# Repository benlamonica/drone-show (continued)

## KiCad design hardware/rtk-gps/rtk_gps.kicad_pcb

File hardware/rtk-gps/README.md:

# RTK GPS board, rev A

NEO-F10N-00B-20 (L1/L5 raw carrier phase) feeds an RP2350A running RTKLIB, which outputs the fix to the flight controller. An MMC5983MA compass sits on the FC's I2C bus.

- 2-layer board, 45 x 45 x 1.6 mm, corner radius 1.5 mm. 4x M2 holes (2.2 mm) on a 39 mm square, 3 mm in from each edge. All parts are on the top side and the smallest passive is 0603.
- PCBWay rules are in `rtk_gps.kicad_dru` and the project file: 0.15 mm (6 mil) track and space, 0.3/0.65 mm vias, 0.3 mm copper to edge.
- DRC: 0 errors and 0 unconnected; schematic parity is clean. One connection_width warning (a 0.13 mm neck at U1 pin 44, +3V3) and silk-clipped-by-mask warnings remain.
- ERC: clean.

## Connectors
| Ref | Part | Pins |
|---|---|---|
| J1 | JST GH-6, Pixhawk GPS port | 1 +5V, 2 FC_TX (into RP2350 GP5), 3 FC_RX (from GP4), 4 SCL, 5 SDA, 6 GND |
| J2 | JST GH-4, AUX UART (RTCM in) | 1 +5V, 2 AUX_TX (GP8), 3 AUX_RX (GP9), 4 GND |
| J3 | JST SH-3, SWD | Raspberry Pi Debug Probe pinout |
| J4 | U.FL | active antenna, 3.3 V bias through 10R + 27nH |
| J5 | USB-C | flashing/debug; diode-ORed with J1 5V |

## RP2350 pins
GP0 TX to GNSS RXD, GP1 RX from GNSS TXD, GP2 PPS, GP3 GNSS reset, GP4/GP5 UART1 to FC, GP6 EXTINT, GP8/GP9 AUX UART (PIO), GP25 status LED. SW1 is BOOTSEL and SW2 is RESET.

## Notes
- Compass: ArduPilot detects the MMC5983MA (I2C 0x30) as an external compass on the GPS I2C bus. The footprint is based on KiCad's MMC5883MA LGA-16 3x3 footprint, which has the same pin map. Check it against the MMC5983MA datasheet land pattern before ordering.
- Antenna: Taoglas AGVLB.25B.07.0060A (L1/L5 helical, U.FL, Mouser 960-AGVLB.25B070060A) is the suggested replacement for an L1-only helical.
- The firmware needs a GPS+Galileo+BeiDou, L1/L5 build (NFREQ=2); the NEO-F10N has no GLONASS.
- The J2 connector (SM04B-GHS-TB) is on backorder at Mouser until about Feb 2027. Any JST GH 4-pin horizontal SMT part fits, or leave J2 off if corrections come through the FC on J1.

## Regenerating
The scripts in `gen/` build everything from `gen/design.py`. They run in the kicad/kicad:9.0 docker image with Freerouting 1.9: `build.sh` does a full re-route, `post.sh` reuses the existing routes, and `gen/export.sh` writes `fab/`.

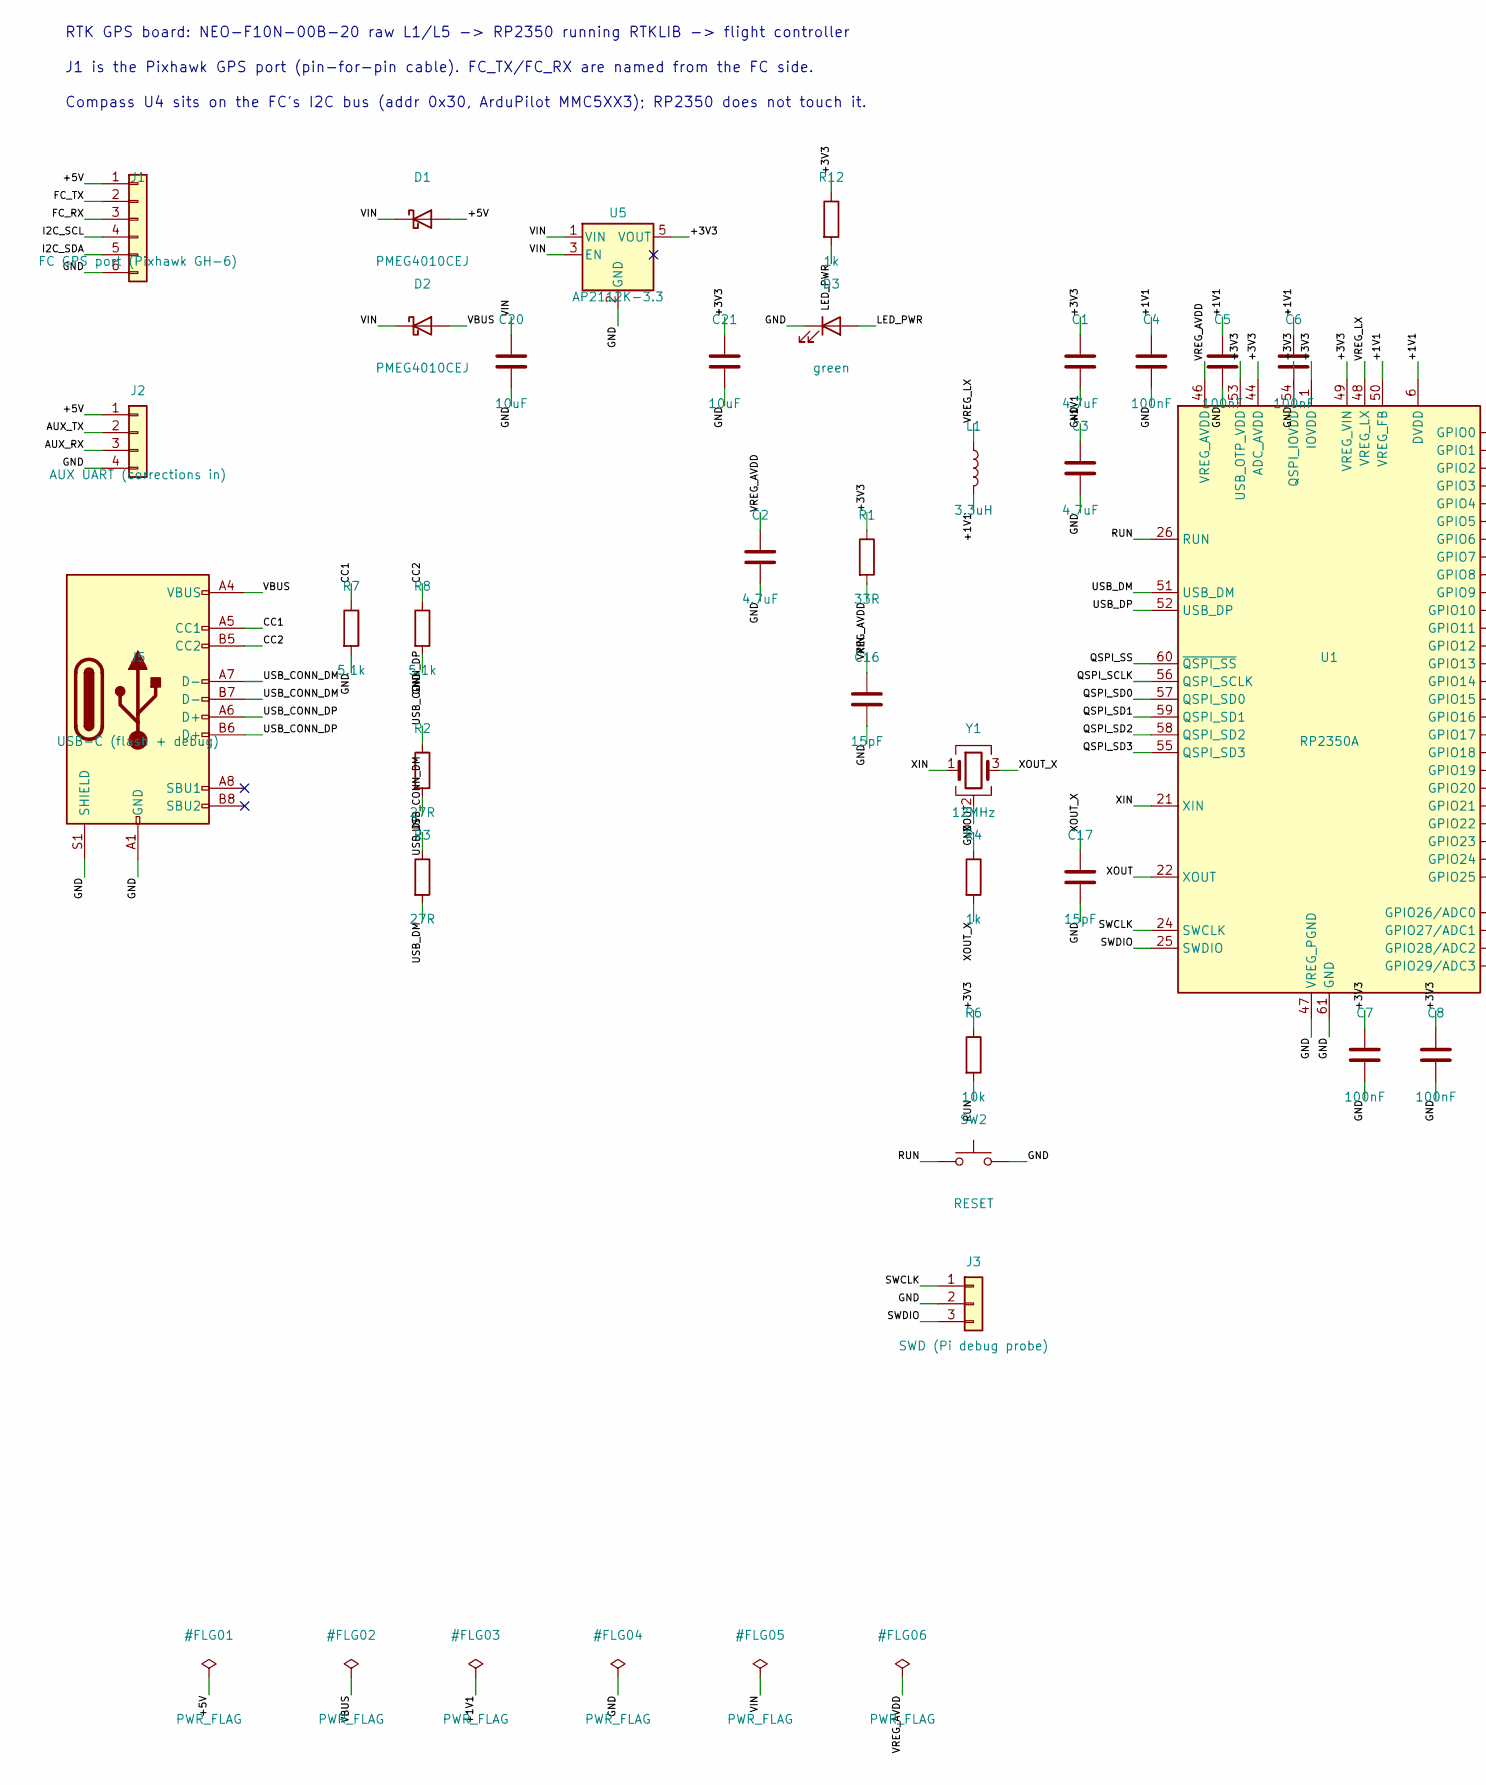
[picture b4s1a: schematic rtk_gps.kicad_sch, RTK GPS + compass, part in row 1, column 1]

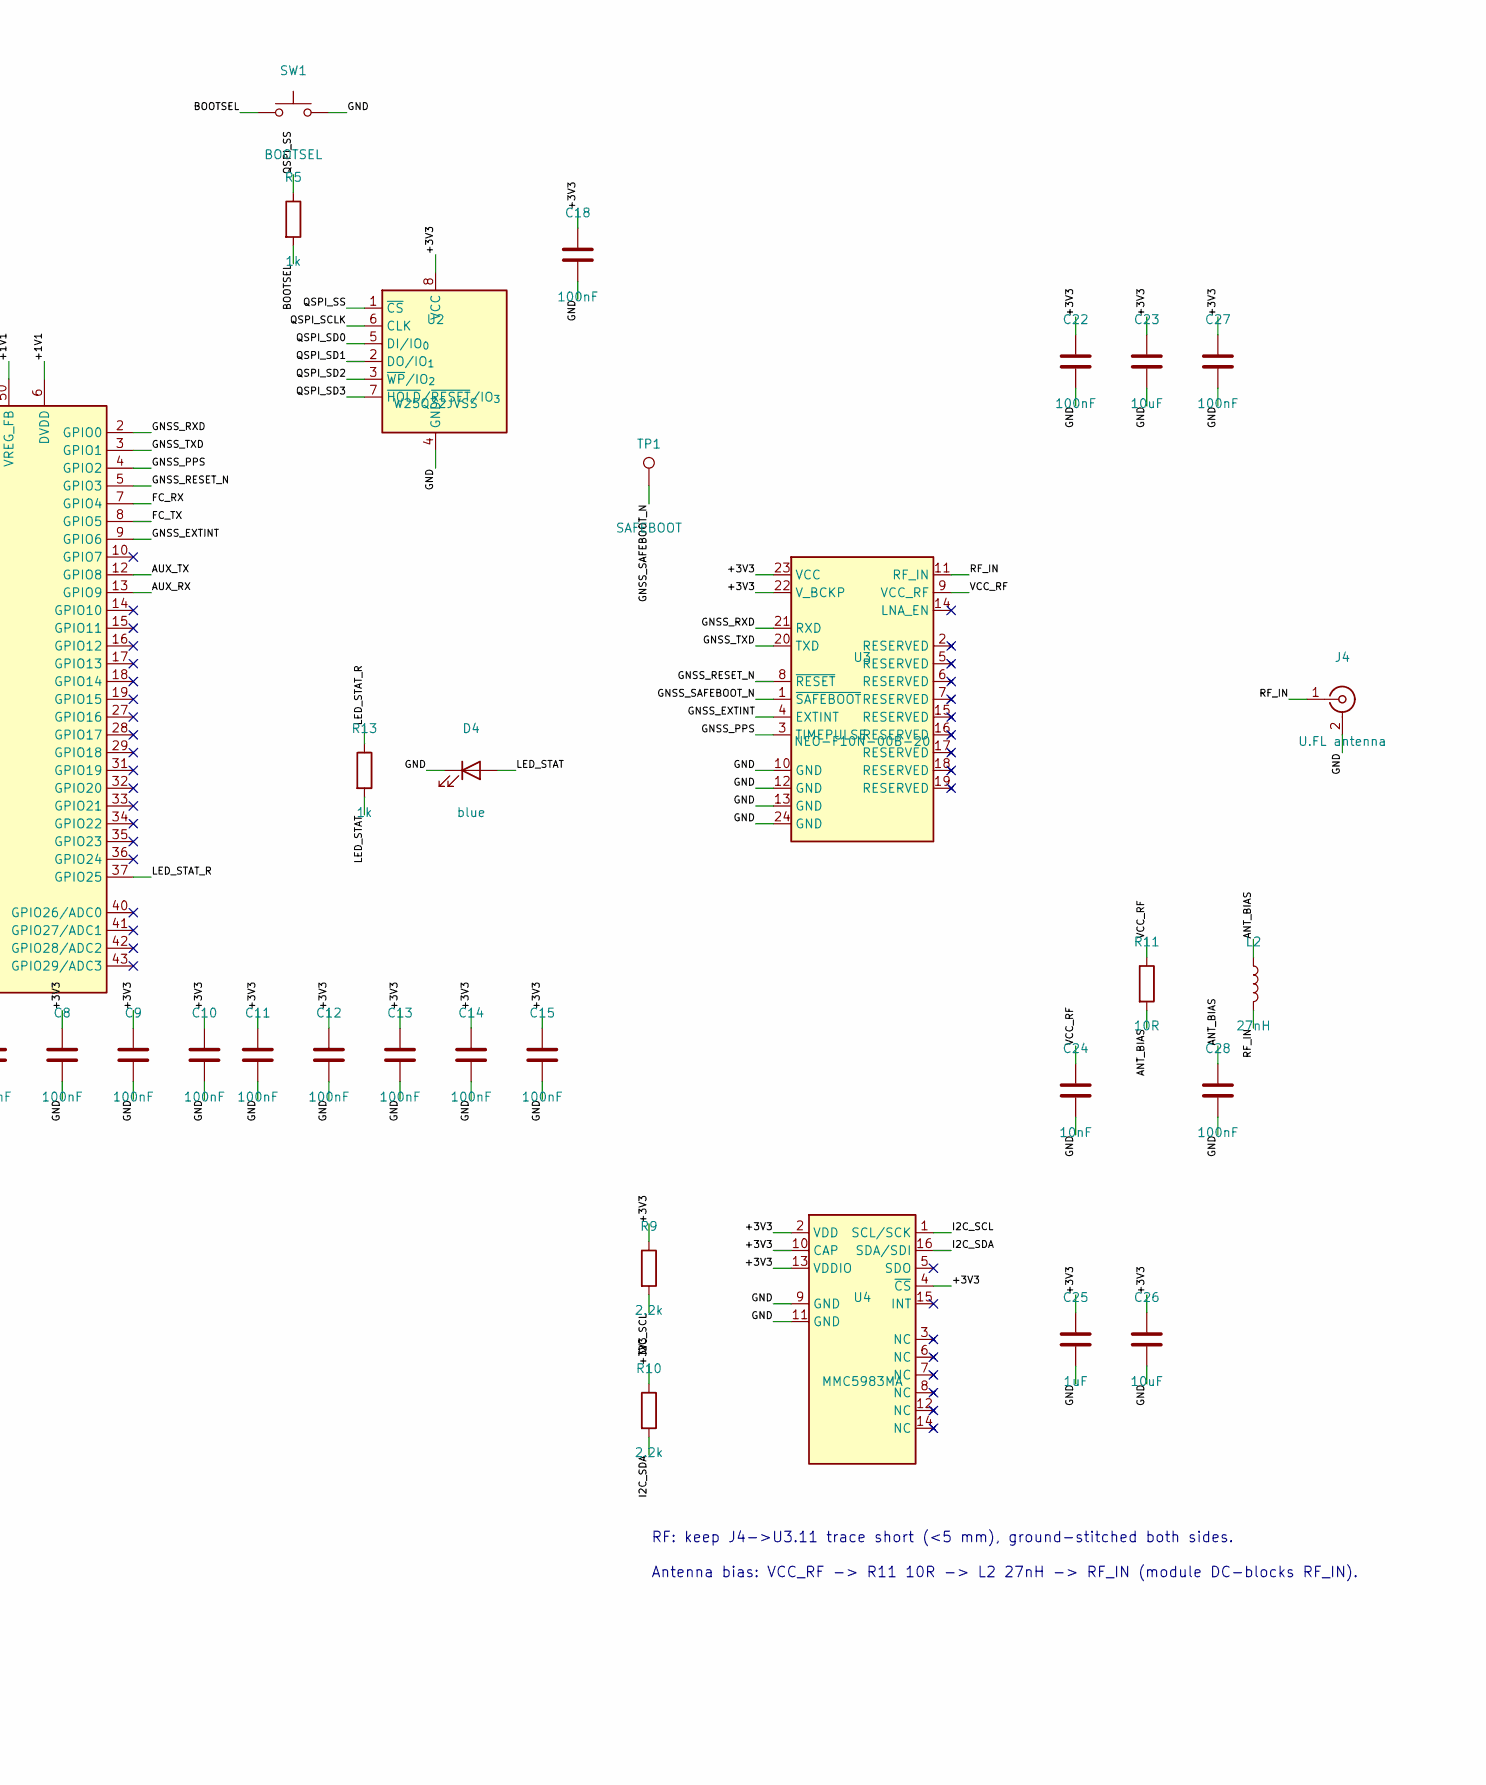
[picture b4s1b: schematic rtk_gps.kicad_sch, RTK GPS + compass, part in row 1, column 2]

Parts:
C1, C2, C3: 4.7uF; C_0603_1608Metric; MPN CL10A475MO8NNNC; Mouser 187-CL10A475MO8NNNC
C4, C5, C6, C7, C8, C9, C10, C11, C12, C13, C14, C15, C18, C22, C27, C28: 100nF; C_0603_1608Metric; MPN CC0603KRX7R7BB104; Mouser 603-CC603KRX7R7BB104
C16, C17: 15pF; C_0603_1608Metric; MPN CC0603JRNPO9BN150; Mouser 603-CC603JRNPO9BN150
C20, C21: 10uF; C_0805_2012Metric; MPN CC0805KKX5R7BB106; Mouser 603-CC805KKX5R7BB106
C23, C26: 10uF; C_0603_1608Metric; MPN LMK107BBJ106MALT; Mouser 963-LMK107BBJ106MALT
C24: 10nF; C_0603_1608Metric; MPN CC0603KRX7R9BB103; Mouser 603-CC603KRX7R9BB103
C25: 1uF; C_0603_1608Metric; MPN CC0603KRX7R7BB105; Mouser 603-CC603KRX7R7BB105
D1, D2: PMEG4010CEJ; D_SOD-323F; MPN PMEG4010CEJ,115; Mouser 771-PMEG4010CEJ-T/R
D3: green; LED_0603_1608Metric; MPN LTST-C191KGKT; Mouser 859-LTST-C191KGKT
D4: blue; LED_0603_1608Metric; MPN LTST-C191TBKT; Mouser 859-LTST-C191TBKT
J1: FC GPS port (Pixhawk GH-6); JST_GH_SM06B-GHS-TB_1x06-1MP_P1.25mm_Horizontal; MPN SM06B-GHS-TB(LF)(SN); Mouser 306-SM06BGHSTBLFSN
J2: AUX UART (corrections in); JST_GH_SM04B-GHS-TB_1x04-1MP_P1.25mm_Horizontal; MPN SM04B-GHS-TB(LF)(SN); Mouser 306-SM04BGHSTBLFSN
J3: SWD (Pi debug probe); JST_SH_SM03B-SRSS-TB_1x03-1MP_P1.00mm_Horizontal; MPN SM03B-SRSS-TB(LF)(SN); Mouser 306-SM03BSRSSTBLFSNP
J4: U.FL antenna; U.FL_Hirose_U.FL-R-SMT-1_Vertical; MPN U.FL-R-SMT-1(10); Mouser 798-U.FL-R-SMT-1-10
J5: USB-C (flash + debug); USB_C_Receptacle_GCT_USB4105-xx-A_16P_TopMnt_Horizontal; MPN USB4105-GF-A; Mouser 640-USB4105-GF-A
L1: 3.3uH; L_Murata_DFE201610P; MPN AOTA-B201610S3R3-101-T; Mouser 815-AB201610S3R3101T
L2: 27nH; L_0603_1608Metric; MPN LQG18HN27NJ00D; Mouser 81-LQG18HN27NJ00D
R1: 33R; R_0603_1608Metric; MPN RC0603FR-0733RL; Mouser 603-RC0603FR-0733RL
R2, R3: 27R; R_0603_1608Metric; MPN RC0603FR-0727RL; Mouser 603-RC0603FR-0727RL
R4, R5, R12, R13: 1k; R_0603_1608Metric; MPN RC0603FR-071KL; Mouser 603-RC0603FR-071KL
R6: 10k; R_0603_1608Metric; MPN RC0603FR-0710KL; Mouser 603-RC0603FR-0710KL
R7, R8: 5.1k; R_0603_1608Metric; MPN RC0603FR-075K1L; Mouser 603-RC0603FR-075K1L
R9, R10: 2.2k; R_0603_1608Metric; MPN RC0603FR-072K2L; Mouser 603-RC0603FR-072K2L
R11: 10R; R_0603_1608Metric; MPN RC0603FR-0710RL; Mouser 603-RC0603FR-0710RL
SW1: BOOTSEL; SW_SPST_B3U-1000P; MPN B3U-1000P; Mouser 653-B3U-1000P
SW2: RESET; SW_SPST_B3U-1000P; MPN B3U-1000P; Mouser 653-B3U-1000P
TP1: SAFEBOOT; TestPoint_Pad_D1.0mm
U1: RP2350A; QFN-60-1EP_7x7mm_P0.4mm_EP3.4x3.4mm; MPN SC1509-A4 (RP2350A); Mouser 358-SC1509
U2: W25Q32JVSS; SOIC-8_5.3x5.3mm_P1.27mm; MPN W25Q32JVSSIQ; Mouser 454-W25Q32JVSSIQ
U3: NEO-F10N-00B-20; ublox_NEO; MPN NEO-F10N-00B-20; Mouser 377-NEO-F10N-00B-20
U4: MMC5983MA; LGA-16_3x3mm_P0.5mm; MPN MMC5983MA; Mouser 438-MMC5983MA
U5: AP2112K-3.3; SOT-23-5; MPN AP2112K-3.3TRG1; Mouser 621-AP2112K-3.3TRG1
Y1: 12MHz; Crystal_SMD_3225-4Pin_3.2x2.5mm; MPN ABM8-272-T3; Mouser 815-ABM8-272-T3

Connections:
/+1V1: C3.1, C4.1, C5.1, C6.1, L1.2, U1.6 (DVDD), U1.23 (DVDD), U1.39 (DVDD), U1.50 (VREG_FB)
/+3V3: C1.1, C7.1, C8.1, C9.1, C10.1, C11.1, C12.1, C13.1, C14.1, C15.1, C18.1, C21.1, C22.1, C23.1, C25.1, C26.1, C27.1, R1.1, R6.1, R9.1, R10.1, R12.1, U1.1 (IOVDD), U1.11 (IOVDD), U1.20 (IOVDD), U1.30 (IOVDD), U1.38 (IOVDD), U1.44 (ADC_AVDD), U1.45 (IOVDD), U1.49 (VREG_VIN), U1.53 (USB_OTP_VDD), U1.54 (QSPI_IOVDD), U2.8 (VCC), U3.22 (V_BCKP), U3.23 (VCC), U4.2 (VDD), U4.4 (~CS), U4.10 (CAP), U4.13 (VDDIO), U5.5 (VOUT)
/+5V: D1.2 (A), J1.1, J2.1
/ANT_BIAS: C28.1, L2.1, R11.2
/AUX_RX: J2.3, U1.13 (GPIO9)
/AUX_TX: J2.2, U1.12 (GPIO8)
/BOOTSEL: R5.2, SW1.1
/CC1: J5.A5 (CC1), R7.1
/CC2: J5.B5 (CC2), R8.1
/FC_RX: J1.3, U1.7 (GPIO4)
/FC_TX: J1.2, U1.8 (GPIO5)
/GND: C1.2, C2.2, C3.2, C4.2, C5.2, C6.2, C7.2, C8.2, C9.2, C10.2, C11.2, C12.2, C13.2, C14.2, C15.2, C16.2, C17.2, C18.2, C20.2, C21.2, C22.2, C23.2, C24.2, C25.2, C26.2, C27.2, C28.2, D3.1 (K), D4.1 (K), J1.6, J2.4, J3.2, J4.2 (Ext), J5.A1 (GND), J5.A12 (GND), J5.B1 (GND), J5.B12 (GND), J5.S1 (SHIELD), R7.2, R8.2, SW1.2, SW2.2, U1.47 (VREG_PGND), U1.61 (GND), U2.4 (GND), U3.10 (GND), U3.12 (GND), U3.13 (GND), U3.24 (GND), U4.9 (GND), U4.11 (GND), U5.2 (GND), Y1.2 (G), Y1.4 (G)
/GNSS_EXTINT: U1.9 (GPIO6), U3.4 (EXTINT)
/GNSS_PPS: U1.4 (GPIO2), U3.3 (TIMEPULSE)
/GNSS_RESET_N: U1.5 (GPIO3), U3.8 (~RESET)
/GNSS_RXD: U1.2 (GPIO0), U3.21 (RXD)
/GNSS_SAFEBOOT_N: TP1.1, U3.1 (~SAFEBOOT)
/GNSS_TXD: U1.3 (GPIO1), U3.20 (TXD)
/I2C_SCL: J1.4, R9.2, U4.1 (SCL/SCK)
/I2C_SDA: J1.5, R10.2, U4.16 (SDA/SDI)
/LED_PWR: D3.2 (A), R12.2
/LED_STAT: D4.2 (A), R13.2
/LED_STAT_R: R13.1, U1.37 (GPIO25)
/QSPI_SCLK: U1.56 (QSPI_SCLK), U2.6 (CLK)
/QSPI_SD0: U1.57 (QSPI_SD0), U2.5 (DI/IO_{0})
/QSPI_SD1: U1.59 (QSPI_SD1), U2.2 (DO/IO_{1})
/QSPI_SD2: U1.58 (QSPI_SD2), U2.3 (~WP/IO_{2})
/QSPI_SD3: U1.55 (QSPI_SD3), U2.7 (~HOLD/~RESET/IO_{3})
/QSPI_SS: R5.1, U1.60 (~QSPI_SS), U2.1 (~CS)
/RF_IN: J4.1 (In), L2.2, U3.11 (RF_IN)
/RUN: R6.2, SW2.1, U1.26 (RUN)
/SWCLK: J3.1, U1.24 (SWCLK)
/SWDIO: J3.3, U1.25 (SWDIO)
/USB_CONN_DM: J5.A7 (D-), J5.B7 (D-), R3.1
/USB_CONN_DP: J5.A6 (D+), J5.B6 (D+), R2.1
/USB_DM: R3.2, U1.51 (USB_DM)
/USB_DP: R2.2, U1.52 (USB_DP)
/VBUS: D2.2 (A), J5.A4 (VBUS), J5.A9 (VBUS), J5.B4 (VBUS), J5.B9 (VBUS)
/VCC_RF: C24.1, R11.1, U3.9 (VCC_RF)
/VIN: C20.1, D1.1 (K), D2.1 (K), U5.1 (VIN), U5.3 (EN)
/VREG_AVDD: C2.1, R1.2, U1.46 (VREG_AVDD)
/VREG_LX: L1.1, U1.48 (VREG_LX)
/XIN: C16.1, U1.21 (XIN), Y1.1
/XOUT: R4.1, U1.22 (XOUT)
/XOUT_X: C17.1, R4.2, Y1.3

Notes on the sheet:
RTK GPS board: NEO-F10N-00B-20 raw L1/L5 -> RP2350 running RTKLIB -> flight controller
J1 is the Pixhawk GPS port (pin-for-pin cable). FC_TX/FC_RX are named from the FC side.
Compass U4 sits on the FC's I2C bus (addr 0x30, ArduPilot MMC5XX3); RP2350 does not touch it.
RF: keep J4->U3.11 trace short (<5 mm), ground-stitched both sides.
Antenna bias: VCC_RF -> R11 10R -> L2 27nH -> RF_IN (module DC-blocks RF_IN).

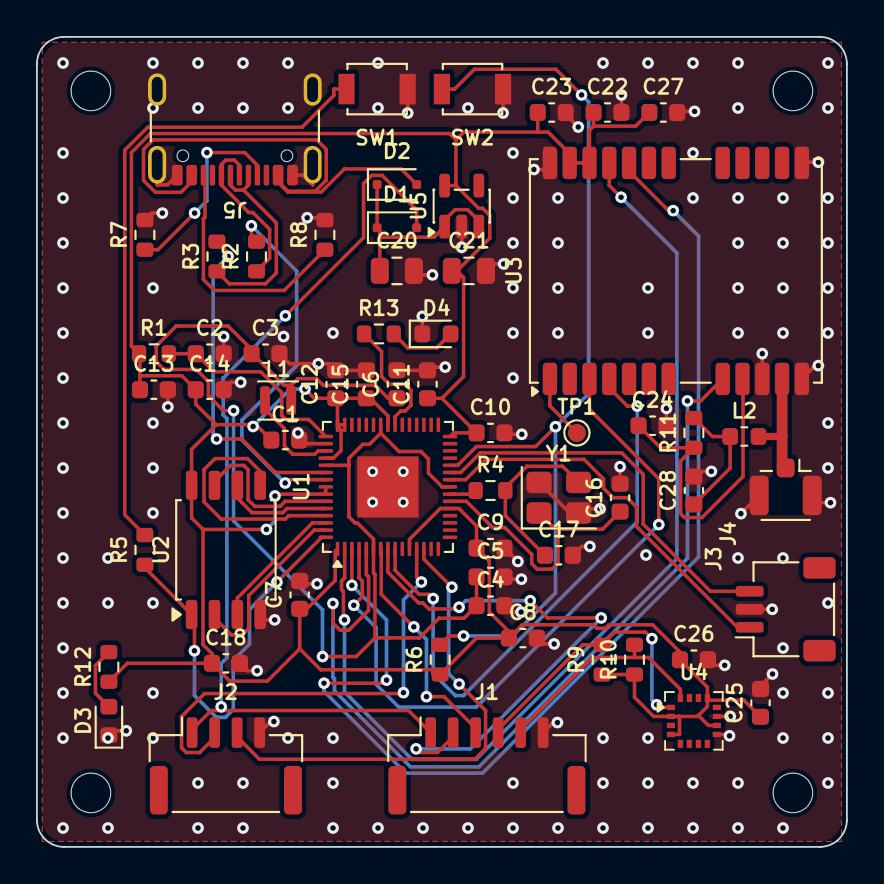
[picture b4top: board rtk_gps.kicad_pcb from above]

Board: 2 copper layers, 45.0 x 45.0 mm, 64 parts (0 on the bottom side), 45 nets.

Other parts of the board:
H1, H2, H3, H4: MountingHole_2.2mm_M2

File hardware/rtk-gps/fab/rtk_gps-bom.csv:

"Designator","Value","Footprint","MPN","Manufacturer","Mouser","Qty"
"C1-C3","4.7uF","Capacitor_SMD:C_0603_1608Metric","CL10A475MO8NNNC","Samsung","187-CL10A475MO8NNNC","3"
"C4-C15,C18,C22,C27,C28","100nF","Capacitor_SMD:C_0603_1608Metric","CC0603KRX7R7BB104","Yageo","603-CC603KRX7R7BB104","16"
"C16,C17","15pF","Capacitor_SMD:C_0603_1608Metric","CC0603JRNPO9BN150","Yageo","603-CC603JRNPO9BN150","2"
"C20,C21","10uF","Capacitor_SMD:C_0805_2012Metric","CC0805KKX5R7BB106","Yageo","603-CC805KKX5R7BB106","2"
"C23,C26","10uF","Capacitor_SMD:C_0603_1608Metric","LMK107BBJ106MALT","Taiyo Yuden","963-LMK107BBJ106MALT","2"
"C24","10nF","Capacitor_SMD:C_0603_1608Metric","CC0603KRX7R9BB103","Yageo","603-CC603KRX7R9BB103","1"
"C25","1uF","Capacitor_SMD:C_0603_1608Metric","CC0603KRX7R7BB105","Yageo","603-CC603KRX7R7BB105","1"
"D1,D2","PMEG4010CEJ","Diode_SMD:D_SOD-323F","PMEG4010CEJ,115","Nexperia","771-PMEG4010CEJ-T/R","2"
"D3","green","LED_SMD:LED_0603_1608Metric","LTST-C191KGKT","Lite-On","859-LTST-C191KGKT","1"
"D4","blue","LED_SMD:LED_0603_1608Metric","LTST-C191TBKT","Lite-On","859-LTST-C191TBKT","1"
"J1","FC GPS port (Pixhawk GH-6)","Connector_JST:JST_GH_SM06B-GHS-TB_1x06-1MP_P1.25mm_Horizontal","SM06B-GHS-TB(LF)(SN)","JST","306-SM06BGHSTBLFSN","1"
"J2","AUX UART (corrections in)","Connector_JST:JST_GH_SM04B-GHS-TB_1x04-1MP_P1.25mm_Horizontal","SM04B-GHS-TB(LF)(SN)","JST","306-SM04BGHSTBLFSN","1"
"J3","SWD (Pi debug probe)","Connector_JST:JST_SH_SM03B-SRSS-TB_1x03-1MP_P1.00mm_Horizontal","SM03B-SRSS-TB(LF)(SN)","JST","306-SM03BSRSSTBLFSNP","1"
"J4","U.FL antenna","Connector_Coaxial:U.FL_Hirose_U.FL-R-SMT-1_Vertical","U.FL-R-SMT-1(10)","Hirose","798-U.FL-R-SMT-1-10","1"
"J5","USB-C (flash + debug)","Connector_USB:USB_C_Receptacle_GCT_USB4105-xx-A_16P_TopMnt_Horizontal","USB4105-GF-A","GCT","640-USB4105-GF-A","1"
"L1","3.3uH","Inductor_SMD:L_Murata_DFE201610P","AOTA-B201610S3R3-101-T","Abracon","815-AB201610S3R3101T","1"
"L2","27nH","Inductor_SMD:L_0603_1608Metric","LQG18HN27NJ00D","Murata","81-LQG18HN27NJ00D","1"
"R1","33R","Resistor_SMD:R_0603_1608Metric","RC0603FR-0733RL","Yageo","603-RC0603FR-0733RL","1"
"R2,R3","27R","Resistor_SMD:R_0603_1608Metric","RC0603FR-0727RL","Yageo","603-RC0603FR-0727RL","2"
"R4,R5,R12,R13","1k","Resistor_SMD:R_0603_1608Metric","RC0603FR-071KL","Yageo","603-RC0603FR-071KL","4"
"R6","10k","Resistor_SMD:R_0603_1608Metric","RC0603FR-0710KL","Yageo","603-RC0603FR-0710KL","1"
"R7,R8","5.1k","Resistor_SMD:R_0603_1608Metric","RC0603FR-075K1L","Yageo","603-RC0603FR-075K1L","2"
"R9,R10","2.2k","Resistor_SMD:R_0603_1608Metric","RC0603FR-072K2L","Yageo","603-RC0603FR-072K2L","2"
"R11","10R","Resistor_SMD:R_0603_1608Metric","RC0603FR-0710RL","Yageo","603-RC0603FR-0710RL","1"
"SW1","BOOTSEL","Button_Switch_SMD:SW_SPST_B3U-1000P","B3U-1000P","Omron","653-B3U-1000P","1"
"SW2","RESET","Button_Switch_SMD:SW_SPST_B3U-1000P","B3U-1000P","Omron","653-B3U-1000P","1"
"U1","RP2350A","Package_DFN_QFN:QFN-60-1EP_7x7mm_P0.4mm_EP3.4x3.4mm","SC1509-A4 (RP2350A)","Raspberry Pi","358-SC1509","1"
"U2","W25Q32JVSS","Package_SO:SOIC-8_5.3x5.3mm_P1.27mm","W25Q32JVSSIQ","Winbond","454-W25Q32JVSSIQ","1"
"U3","NEO-F10N-00B-20","RF_GPS:ublox_NEO","NEO-F10N-00B-20","u-blox","377-NEO-F10N-00B-20","1"
"U4","MMC5983MA","Package_LGA:LGA-16_3x3mm_P0.5mm","MMC5983MA","MEMSIC","438-MMC5983MA","1"
"U5","AP2112K-3.3","Package_TO_SOT_SMD:SOT-23-5","AP2112K-3.3TRG1","Diodes Inc","621-AP2112K-3.3TRG1","1"
"Y1","12MHz","Crystal:Crystal_SMD_3225-4Pin_3.2x2.5mm","ABM8-272-T3","Abracon","815-ABM8-272-T3","1"
